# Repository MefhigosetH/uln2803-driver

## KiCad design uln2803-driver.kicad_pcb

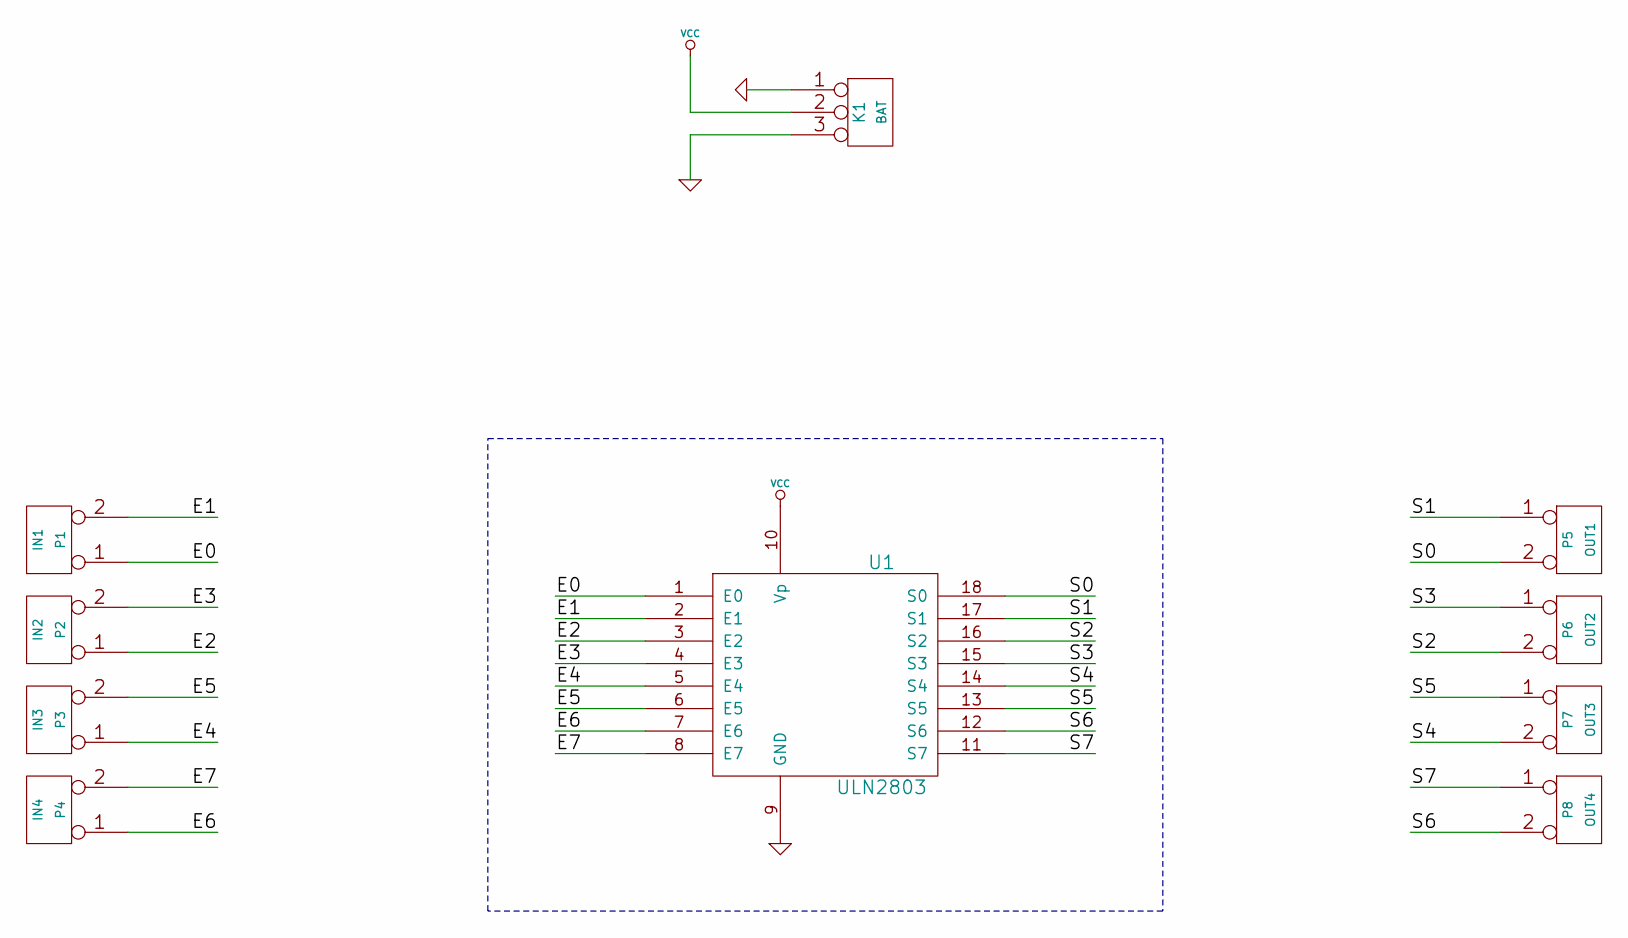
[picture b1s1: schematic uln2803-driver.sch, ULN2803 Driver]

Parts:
K1: BAT
P1: IN1
P2: IN2
P3: IN3
P4: IN4
P5: OUT1
P6: OUT2
P7: OUT3
P8: OUT4
U1: ULN2803

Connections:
/E0: P1.1, U1.1 (E0)
/E1: P1.2 (PM), U1.2 (E1)
/E2: P2.1, U1.3 (E2)
/E3: P2.2 (PM), U1.4 (E3)
/E4: P3.1, U1.5 (E4)
/E5: P3.2 (PM), U1.6 (E5)
/E6: P4.1, U1.7 (E6)
/E7: P4.2 (PM), U1.8 (E7)
/S0: P5.2 (PM), U1.18 (S0)
/S1: P5.1, U1.17 (S1)
/S2: P6.2 (PM), U1.16 (S2)
/S3: P6.1, U1.15 (S3)
/S4: P7.2 (PM), U1.14 (S4)
/S5: P7.1, U1.13 (S5)
/S6: P8.2 (PM), U1.12 (S6)
/S7: P8.1, U1.11 (S7)
GND: K1.1, K1.3, U1.9 (GND)
VCC: K1.2 (PM), U1.10 (Vp)

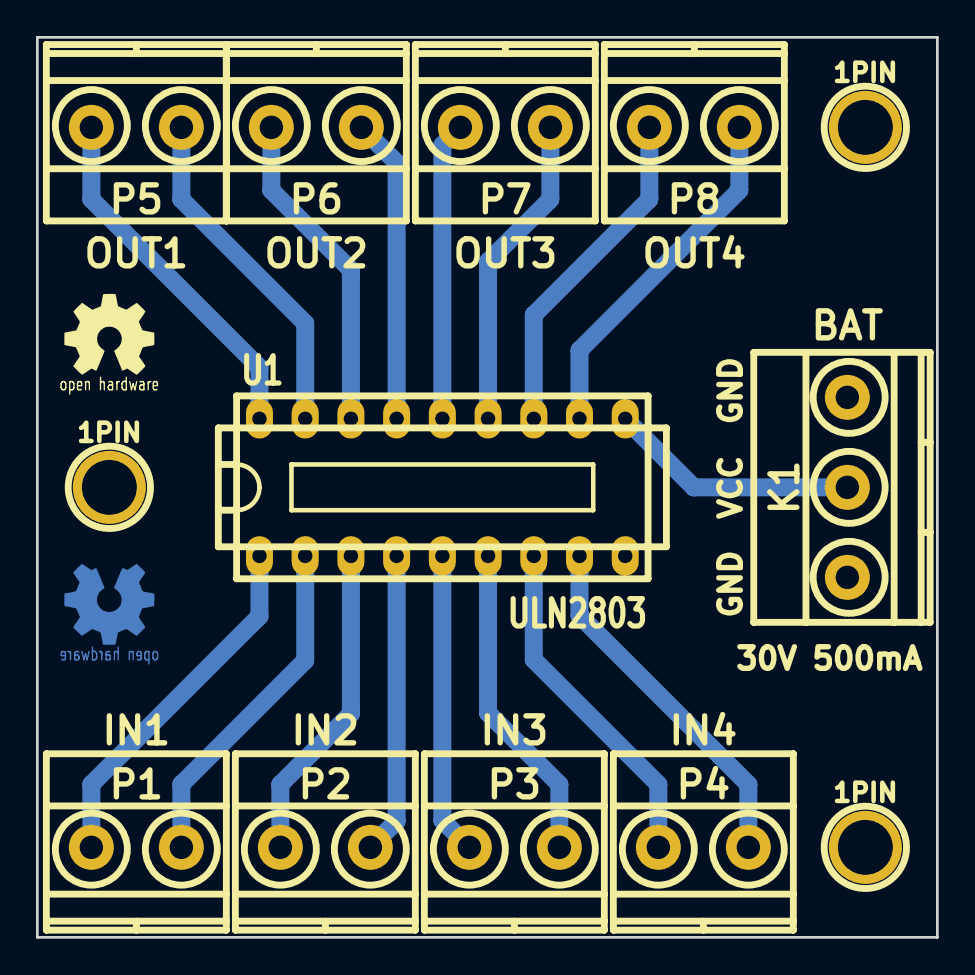
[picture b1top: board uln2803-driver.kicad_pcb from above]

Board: 2 copper layers, 50.0 x 50.0 mm, 13 parts (0 on the bottom side), 18 nets.

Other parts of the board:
1PIN, 1PIN#2, 1PIN#3: P***; 1pin

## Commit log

2014-11-06 Changed borniers from mpt with 2,54mm pitch to mkds with 5mm pitch. Added filled zones to connect GND.
